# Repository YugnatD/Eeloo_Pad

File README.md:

# Eeloo Pad
## A Kerbal Space Program Control Panel
A Open Source project to create a control panel for Kerbal Space Program. The goal is to create a control panel that can be used to control the game from a physical panel. The control panel will be able to control the game, and display information about the game.

## Features
* Control the game (Thrust, SAS, RCS, etc.)
* TODO

## Block Diagram
[Diagram](https://app.diagrams.net/#G1_EMb1VFjsUEVt7AdRK-4kCuMEsyWomvp)

## Schematic

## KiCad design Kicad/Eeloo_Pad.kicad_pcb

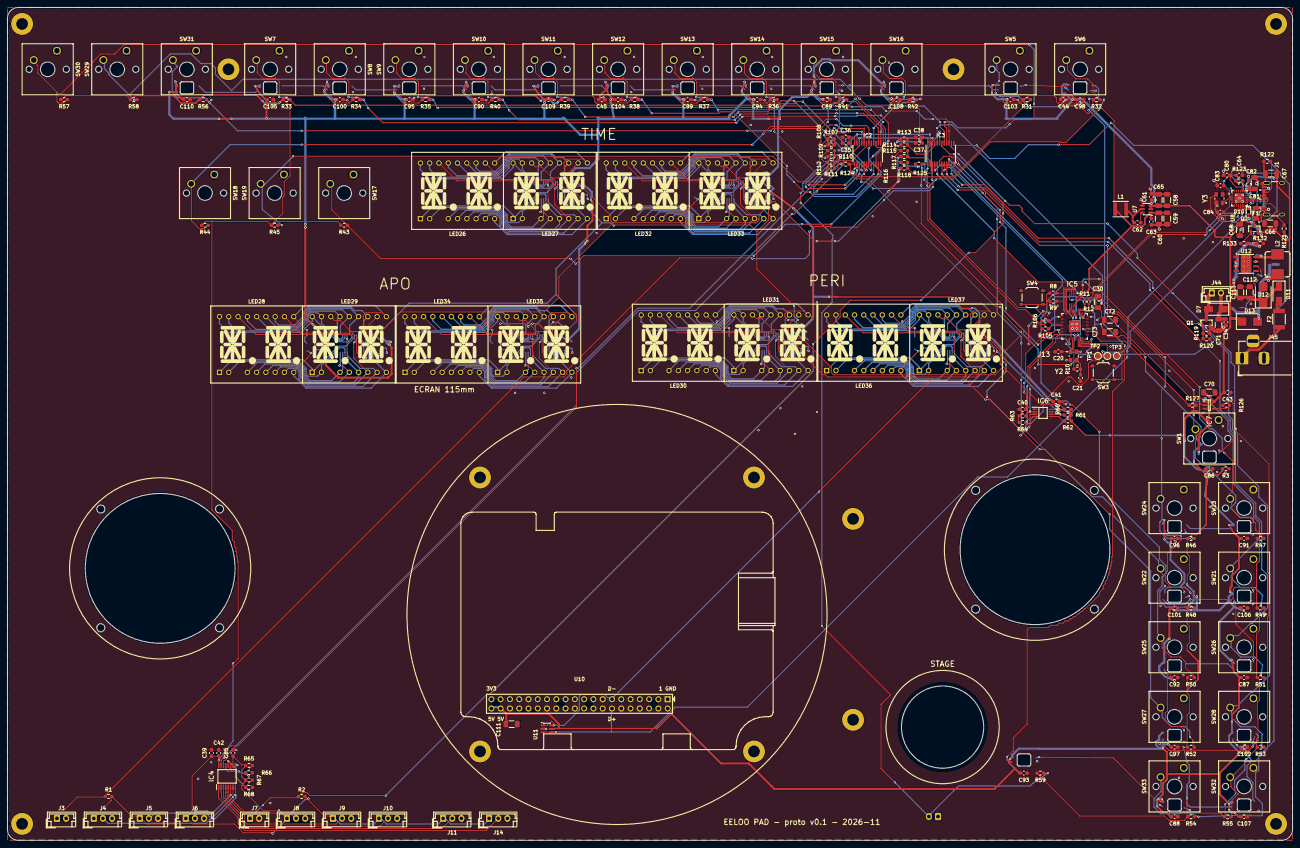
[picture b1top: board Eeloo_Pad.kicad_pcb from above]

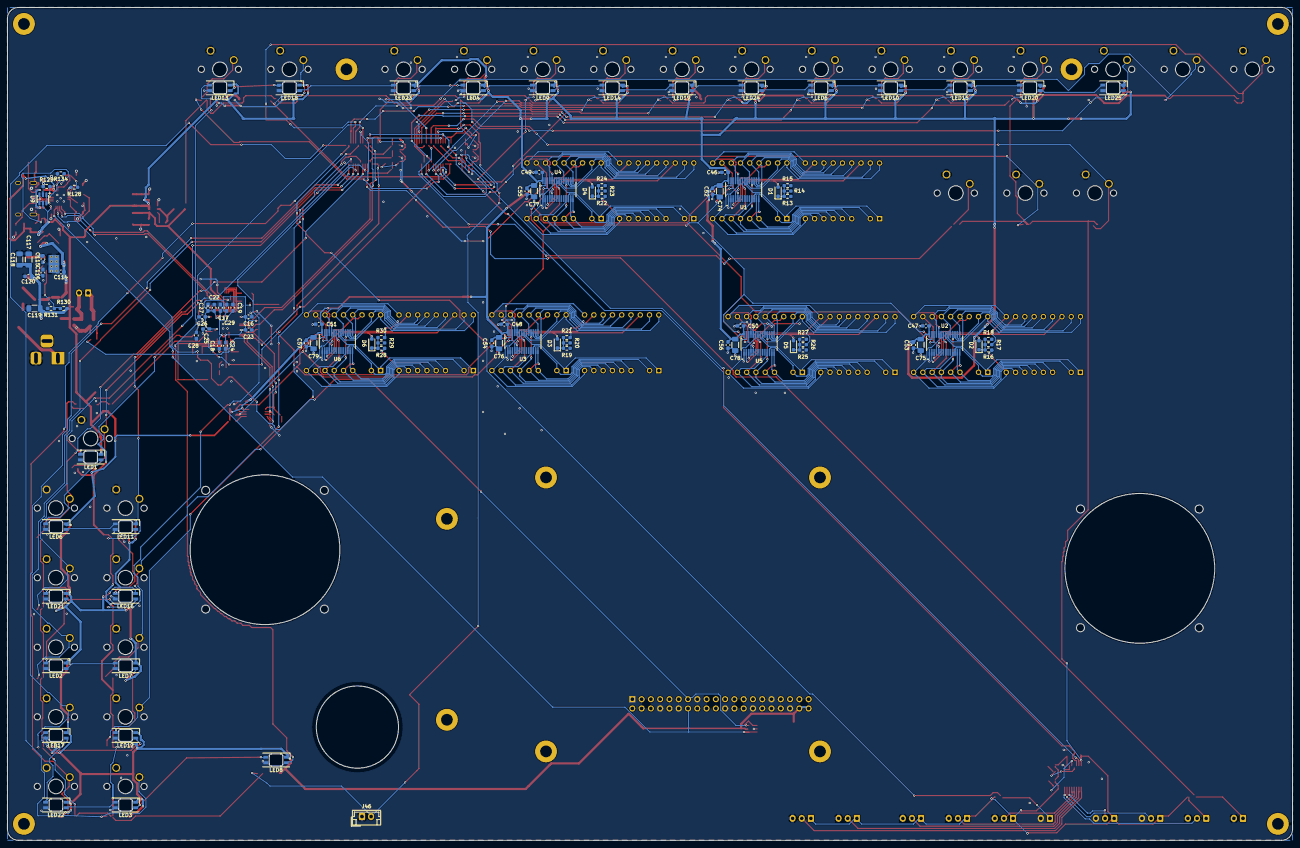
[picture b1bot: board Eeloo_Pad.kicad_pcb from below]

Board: 2 copper layers, 351.8 x 228.0 mm, 333 parts (99 on the bottom side), 253 nets.

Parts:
C16, C18, C19, C23, C24, C25, C26, C27, C28, C29, C34, C35, C36, C37, C38, C39, C40, C41, C42, C43, C44, C45, C46, C47, C48, C49, C50, C51, C52, C53, C54, C55, C56, C57, C64, C82, C85, C86, C87, C88, C89, C90, C91, C92, C93, C94, C95, C96, C97, C98, C99, C100, C101, C102, C103, C104, C105, C106, C107, C108, C109, C110: 100n; C_0603_1608Metric_Pad1.08x0.95mm_HandSolder
C17, C22, C80: 1u; C_0603_1608Metric_Pad1.08x0.95mm_HandSolder
C20, C21, C83, C84: 15p; C_0603_1608Metric_Pad1.08x0.95mm_HandSolder
C30, C81, C111: 10u; C_1206_3216Metric_Pad1.33x1.80mm_HandSolder
C58, C59, C60, C65, C66, C67, C68, C70, C71, C72, C73, C74, C75, C76, C77, C78, C79, C117, C118, C119: 22uF; C_1206_3216Metric_Pad1.33x1.80mm_HandSolder
C61, C62, C63, C114, C115, C120: 100nF; C_0603_1608Metric_Pad1.08x0.95mm_HandSolder
C112, C113: 10uF; C_1206_3216Metric_Pad1.33x1.80mm_HandSolder
C116: 1uF; C_0603_1608Metric_Pad1.08x0.95mm_HandSolder
D1, D2, D3, D4, D5, D6: SD103AWS; D_SOD-323_HandSoldering
D7, D11: SS34; D_SMA
D10: ESD5Zxx; D_SOD-523
D12: SMBJ15CA; D_SMB
D13: SS54; D_SMB
F1: 1.5A; Fuse_1206_3216Metric
F2: 2A; Fuse_1812_4532Metric_Pad1.30x3.40mm_HandSolder
H1, H2, H3, H4, H5, H6, H7, H8, H9, H10, H11, H12: MountingHole_3.2mm_M3_Pad
H13: XB2-BS542 22.5mm; Schneider_XB2_22.5mm_PanelMount
IC2, IC3: PCA9535PW; TSSOP-24_4.4x7.8mm_P0.65mm
IC4: ADS7830IPWR; SOP65P640X120-16N
IC5: W25Q16JVUXIQ_TR; SON50P300X200X60-9N
IC6: TCA9617ADGKR; SOP65P490X110-8N
IC7: SN74AHCT1G125DBVR; SOT95P280X145-5N
J1: USB_C_Receptacle_USB2.0_16P; USB_C_Receptacle_HCTL_HC-TYPE-C-16P-01A
J3, J7, J44: Conn_01x02_Pin; JST_EH_B2B-EH-A_1x02_P2.50mm_Vertical
J4, J5, J6, J8, J9, J10, J11, J14: Conn_01x03_Pin; JST_EH_B3B-EH-A_1x03_P2.50mm_Vertical
J13: SC0914_13_; SC091413
J45: Jack 12V 5.5x2.1; BarrelJack_Horizontal
J46: XB2-BS542 STAGE; JST_EH_B2B-EH-A_1x02_P2.50mm_Vertical
JS1, JS2: R400B-M2
L1: 3.9uH; L_Sunlord_SWPA4030S
L2: 8.2uH; L_Bourns_SRP7028A_7.3x6.6mm
LED1, LED2, LED3, LED4, LED5, LED6, LED7, LED8, LED9, LED10, LED11, LED12, LED13, LED14, LED15, LED16, LED17, LED18, LED19, LED20, LED21, LED22, LED23, LED24, LED25: SK6812MINI-EA; LED_SK6812MINI-E_3.2x2.8mm
LED26, LED27, LED28, LED29, LED30, LED31, LED32, LED33, LED34, LED35, LED36, LED37: FJ5241AH; LED-SEG-TH_18P-L25.2-W21.1-P2.54-LS15.2-BL
Q1: AO3400A; SOT-23
Q2: AO3401A; SOT-23
R1, R2, R3, R31, R32, R33, R34, R35, R36, R37, R38, R39, R40, R41, R42, R43, R44, R45, R46, R47, R48, R49, R50, R51, R52, R53, R54, R55, R56, R57, R58, R59, R62, R65, R66, R67, R68, R107, R108, R109, R110, R111, R112, R113, R114, R115, R116, R117, R118, R119, R123, R124, R125, R127, R128, R129: 10k; R_0603_1608Metric_Pad0.98x0.95mm_HandSolder
R8, R10: 1k; R_0603_1608Metric_Pad0.98x0.95mm_HandSolder
R9: NC; R_0603_1608Metric_Pad0.98x0.95mm_HandSolder
R11, R12: 27.4; R_0402_1005Metric_Pad0.72x0.64mm_HandSolder
R13, R14, R15, R16, R17, R18, R19, R20, R21, R22, R23, R24, R25, R26, R27, R28, R29, R30: 39k; R_0603_1608Metric_Pad0.98x0.95mm_HandSolder
R60, R61, R63, R64, R105, R106: 4k7; R_0603_1608Metric_Pad0.98x0.95mm_HandSolder
R120: 100; R_0603_1608Metric_Pad0.98x0.95mm_HandSolder
R121, R122: 5.1k; R_0603_1608Metric_Pad0.98x0.95mm_HandSolder
R126: 330; R_0603_1608Metric_Pad0.98x0.95mm_HandSolder
R130, R133: 100k; R_0603_1608Metric_Pad0.98x0.95mm_HandSolder
R131: 23.2k; R_0603_1608Metric_Pad0.98x0.95mm_HandSolder
R132: 47k; R_0603_1608Metric_Pad0.98x0.95mm_HandSolder
R134: 15k; R_0603_1608Metric_Pad0.98x0.95mm_HandSolder
SW1, SW5, SW6, SW7, SW8, SW9, SW10, SW11, SW12, SW13, SW14, SW15, SW16, SW17, SW18, SW19, SW21, SW22, SW23, SW24, SW25, SW26, SW27, SW28, SW29, SW30, SW31, SW32, SW33: DUROCK_Ice_King_62g; SW_MX_Transparent_1.00u_PCB
SW3, SW4: SW_Push; SW_Push_1P1T_XKB_TS-1187A
TP1: SWCLK; TestPoint_Pad_D1.5mm
TP2: SWDIO; TestPoint_Pad_D1.5mm
TP3: GND; TestPoint_Pad_D1.5mm
U1, U2, U3, U4, U5, U6: HT16K33A-28SSOP; SOP63P600X175-28N
U7: AP63203WU; TSOT-23-6
U8: CH334F; QFN-24-1EP_4x4mm_P0.5mm_EP2.7x2.7mm
U9, U11: USBLC6-2SC6; SOT-23-6
U10: ESP32-P4-WIFI6-Touch-LCD-3.4C; ESP32-P4_WS_3.4C_Header
U12: LMR33630ADDA; Texas_HSOP-8-1EP_3.9x4.9mm_P1.27mm_ThermalVias
Y2: ABM8-272-T3; ABM8272T3
Y3: 12MHz; ABM8272T3

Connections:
+3.3V: C16.1, C22.1, C23.1, C24.1, C25.1, C26.1, C27.1, C28.1, C29.1, C30.1, C35.1, C36.1, C37.1, C38.1, C39.1, C40.1, C42.1, C59.1, C60.1, C63.1, C72.1, C73.1, C85.1, IC2.24 (VCC), IC3.24 (VCC), IC4.10 (REFIN/REFOUT), IC4.16 (+VDD), IC5.8 (VCC), IC6.1 (VCC(A)), J4.1, J5.1, J6.1, J8.1, J9.1, J10.1, J11.1, J13.1 (IOVDD_1), J13.10 (IOVDD_2), J13.22 (IOVDD_3), J13.33 (IOVDD_4), J13.42 (IOVDD_5), J13.43 (ADC_AVDD), J13.44 (VREG_VIN), J13.48 (USB_VDD), J13.49 (IOVDD_6), J14.1, L1.2, R1.2, R2.2, R3.1, R9.2, R31.1, R32.1, R33.1, R34.1, R35.1, R36.1, R37.1, R38.1, R39.1, R40.1, R41.1, R42.1, R43.1, R44.1, R45.1, R46.1, R47.1, R48.1, R49.1, R50.1, R51.1, R52.1, R53.1, R54.1, R55.1, R56.1, R57.1, R58.1, R59.1, R63.1, R64.1, R65.1, R67.1, R105.1, R106.1, R107.1, R109.1, R111.1, R113.1, R115.1, R117.1, R124.1, R125.1, U7.1 (FB)
+12V: C112.1, C113.1, C114.1, D11.1, D12.1, R132.1, U12.2, U12.3
/BUCK_BOOT: C115.1, U12.7
/BUCK_FB: R130.2, R131.1, U12.5
/BUCK_SW: C115.2, L2.1, U12.8
/BUCK_VCC: C116.1, U12.6
/CC1: J1.A5 (CC1), R121.1
/CC2: J1.B5 (CC2), R122.1
/DC_SENSE: Q2.1, R132.2, R133.1
/HUB_OVCUR: R128.2, U8.1 (~OVCUR)
/HUB_PSELF: R129.1, U8.18 (PSELF)
/HUB_RESET: R123.2, R134.1, U8.16 (~RESET/CDP)
/HUB_V33: C64.1, C80.1, R128.1, U8.20 (VDD33_{LDO})
/USB1_DM: U8.11 (DM1-), U10.13 (GPIO20_27), U11.1 (I/O1), U11.6 (I/O1)
/USB1_DP: U8.12 (DP1+), U10.14 (GND_28), U11.3 (I/O2), U11.4 (I/O2)
/USB2_DM: R12.2, U8.9 (DM2-)
/USB2_DP: R11.2, U8.10 (DP2+)
/USB_DM: J1.A7 (D-), J1.B7 (D-), U8.14 (DMU-), U9.1 (I/O1), U9.6 (I/O1)
/USB_DP: J1.A6 (D+), J1.B6 (D+), U8.15 (DPU+), U9.3 (I/O2), U9.4 (I/O2)
/V5_DC: C117.1, C118.1, C119.1, C120.1, D13.2, L2.2, R130.1
/VBUS: C34.1, C41.1, C43.1, C44.1, C45.1, C46.1, C47.1, C48.1, C49.1, C50.1, C51.1, C52.1, C53.1, C54.1, C55.1, C56.1, C57.1, C58.1, C61.1, C65.1, C66.1, C67.1, C68.1, C70.1, C71.1, C74.1, C75.1, C76.1, C77.1, C78.1, C79.1, C81.1, C82.1, C86.1, C87.1, C88.1, C89.1, C90.1, C91.1, C92.1, C93.1, C94.1, C95.1, C96.1, C97.1, C98.1, C99.1, C100.1, C101.1, C102.1, C103.1, C104.1, C105.1, C106.1, C107.1, C108.1, C109.1, C110.1, C111.1, D7.1 (K), D10.1 (K), D13.1, IC6.8 (VCC(B)), IC7.5 (VCC), J44.2, LED1.1, LED2.1, LED3.1, LED4.1, LED5.1, LED6.1, LED7.1, LED8.1, LED9.1, LED10.1, LED11.1, LED12.1, LED13.1, LED14.1, LED15.1, LED16.1, LED17.1, LED18.1, LED19.1, LED20.1, LED21.1, LED22.1, LED23.1, LED24.1, LED25.1, Q2.2, R60.1, R61.1, R62.1, U1.28 (VDD), U2.28 (VDD), U3.28 (VDD), U4.28 (VDD), U5.28 (VDD), U6.28 (VDD), U7.2 (EN), U7.3 (IN), U8.19 (V5), U9.5 (VBUS), U10.38 (GPIO46_4), U10.40 (GPIO30_2), U11.5 (VBUS)
/VBUS_USB: F1.2, Q2.3, R123.1
/control_module/ANTINORMAL: IC3.7 (P03), R49.2, SW21.2
/control_module/ANTI_MANEUVER: IC3.14 (P11), R55.2, SW32.2
/control_module/ANTI_TARGET: IC3.11 (P07), R53.2, SW28.2
/control_module/BRAKE: IC2.19 (P16), R45.2, SW19.2
/control_module/CIBLE_ORBIT: IC3.15 (P12), R56.2, SW31.2
/control_module/CTRL0: IC2.6 (P02), R33.2, SW7.2
/control_module/CTRL1: IC2.7 (P03), R34.2, SW8.2
/control_module/CTRL2: IC2.8 (P04), R35.2, SW9.2
/control_module/CTRL3: IC2.9 (P05), R36.2, SW14.2
/control_module/CTRL4: IC2.10 (P06), R37.2, SW13.2
/control_module/CTRL5: IC2.11 (P07), R38.2, SW12.2
/control_module/CTRL6: IC2.13 (P10), R39.2, SW11.2
/control_module/CTRL7: IC2.14 (P11), R40.2, SW10.2
/control_module/CTRL8: IC2.15 (P12), R41.2, SW15.2
/control_module/CTRL9: IC2.16 (P13), R42.2, SW16.2
/control_module/EXT1: IC4.1 (CH0), J14.2
/control_module/GEAR: IC2.18 (P15), R44.2, SW18.2
/control_module/I2C0_SCL_33: IC2.22 (SCL), IC3.22 (SCL), IC4.14 (SCL), J13.7 (GPIO5), R105.2
/control_module/I2C0_SDA_33: IC2.23 (SDA), IC3.23 (SDA), IC4.15 (SDA), J13.6 (GPIO4), R106.2
/control_module/I2C1_SCL_33: IC6.2 (SCLA), J13.14 (GPIO11), R63.2
/control_module/I2C1_SCL_50: IC6.7 (SCLB), R60.2, U1.26 (SCL), U2.26 (SCL), U3.26 (SCL), U4.26 (SCL), U5.26 (SCL), U6.26 (SCL)
/control_module/I2C1_SDA_33: IC6.3 (SDAA), J13.13 (GPIO10), R64.2
/control_module/I2C1_SDA_50: IC6.6 (SDAB), R61.2, U1.27 (SDA), U2.27 (SDA), U3.27 (SDA), U4.27 (SDA), U5.27 (SDA), U6.27 (SDA)
/control_module/I2C_GPIO_EXT0_INT: IC2.1 (~INT), J13.18 (GPIO15), R124.2
/control_module/I2C_GPIO_EXT1_INT: IC3.1 (~INT), J13.27 (GPIO16), R125.2
/control_module/JOY_BTN_D: IC3.18 (P15), J7.1, R2.1
/control_module/JOY_BTN_G: IC3.19 (P16), J3.1, R1.1
/control_module/JOY_D_AXIS_R: IC4.3 (CH2), J10.2
/control_module/JOY_D_AXIS_X: IC4.5 (CH4), J8.2
/control_module/JOY_D_AXIS_Y: IC4.4 (CH3), J9.2
/control_module/JOY_G_AXIS_R: IC4.6 (CH5), J6.2
/control_module/JOY_G_AXIS_X: IC4.8 (CH7), J4.2
/control_module/JOY_G_AXIS_Y: IC4.7 (CH6), J5.2
/control_module/LED_CTRL_33: IC7.2 (A), J13.32 (GPIO21), R127.1
/control_module/LED_CTRL_50: IC7.4 (Y), R126.2
/control_module/LIGHT: IC2.17 (P14), R43.2, SW17.2
/control_module/MANEUVER: IC3.13 (P10), R54.2, SW33.2
/control_module/NORMAL: IC3.6 (P02), R48.2, SW22.2
/control_module/ORBIT_SURFACE: IC3.16 (P13), R57.2, SW30.2
/control_module/PROGRADE: IC3.4 (P00), R46.2, SW24.2
/control_module/RADIAL_IN: IC3.8 (P04), R50.2, SW25.2
/control_module/RADIAL_OUT: IC3.9 (P05), R51.2, SW26.2
/control_module/RCS: IC2.5 (P01), R32.2, SW6.2
/control_module/RETROGRADE: IC3.5 (P01), R47.2, SW23.2
/control_module/SAS: IC2.4 (P00), R31.2, SW5.2
/control_module/SEA_EARTH: IC3.17 (P14), R58.2, SW29.2
/control_module/STAB_ASSIST: IC3.20 (P17), R3.2, SW1.2
/control_module/STAGE: IC2.20 (P17), J46.2, R59.2
/control_module/TARGET: IC3.10 (P06), R52.2, SW27.2
/control_module/THROTTLE: IC4.2 (CH1), J11.2
/control_module/VIBRO_CTRL_33: J13.17 (GPIO14), R120.1
/control_module/seg_4x14_module1/A: LED32.12 (A), LED33.12 (A), U4.25 (ROW0/A2)
/control_module/seg_4x14_module1/A0: LED32.9 (C), LED33.9 (C), R22.1, U4.23 (ROW2/A0)
/control_module/seg_4x14_module1/A1: LED32.10 (B), LED33.10 (B), U4.24 (ROW1/A1)
/control_module/seg_4x14_module1/AD: D4.2 (A), LED32.16 (DIG1), U4.2 (COM0/AD)
/control_module/seg_4x14_module1/COM1: LED32.11 (DIG2), U4.3 (COM1/KS0)
/control_module/seg_4x14_module1/COM2: LED33.16 (DIG1), U4.4 (COM2/KS1)
/control_module/seg_4x14_module1/COM3: LED33.11 (DIG2), U4.5 (COM3/KS2)
/control_module/seg_4x14_module1/D: LED32.7 (D), LED33.7 (D), U4.22 (ROW3/K1)
/control_module/seg_4x14_module1/DP: LED32.8 (DP), LED33.8 (DP), U4.11 (ROW14/K12)
/control_module/seg_4x14_module1/E: LED32.1 (E), LED33.1 (E), U4.21 (ROW4/K2)
/control_module/seg_4x14_module1/F: LED32.18 (F), LED33.18 (F), U4.20 (ROW5/K3)
/control_module/seg_4x14_module1/G1: LED32.13 (G1), LED33.13 (G1), U4.19 (ROW6/K4)
/control_module/seg_4x14_module1/G2: LED32.6 (G2), LED33.6 (G2), U4.18 (ROW7/K5)
/control_module/seg_4x14_module1/H: LED32.17 (H), LED33.17 (H), U4.17 (ROW8/K6)
/control_module/seg_4x14_module1/J: LED32.15 (J), LED33.15 (J), U4.16 (ROW9/K7)
/control_module/seg_4x14_module1/K: LED32.14 (K), LED33.14 (K), U4.15 (ROW10/K8)
/control_module/seg_4x14_module1/L: LED32.5 (L), LED33.5 (L), U4.14 (ROW11/K9)
/control_module/seg_4x14_module1/M: LED32.4 (M), LED33.4 (M), U4.13 (ROW12/K10)
/control_module/seg_4x14_module1/N: LED32.2 (N), LED33.2 (N), U4.12 (ROW13/K11)
/control_module/seg_4x14_module2/A: LED34.12 (A), LED35.12 (A), U5.25 (ROW0/A2)
/control_module/seg_4x14_module2/A0: LED34.9 (C), LED35.9 (C), U5.23 (ROW2/A0)
/control_module/seg_4x14_module2/A1: LED34.10 (B), LED35.10 (B), R26.1, U5.24 (ROW1/A1)
/control_module/seg_4x14_module2/AD: D5.2 (A), LED34.16 (DIG1), U5.2 (COM0/AD)
/control_module/seg_4x14_module2/COM1: LED34.11 (DIG2), U5.3 (COM1/KS0)
/control_module/seg_4x14_module2/COM2: LED35.16 (DIG1), U5.4 (COM2/KS1)
/control_module/seg_4x14_module2/COM3: LED35.11 (DIG2), U5.5 (COM3/KS2)
/control_module/seg_4x14_module2/D: LED34.7 (D), LED35.7 (D), U5.22 (ROW3/K1)
/control_module/seg_4x14_module2/DP: LED34.8 (DP), LED35.8 (DP), U5.11 (ROW14/K12)
/control_module/seg_4x14_module2/E: LED34.1 (E), LED35.1 (E), U5.21 (ROW4/K2)
/control_module/seg_4x14_module2/F: LED34.18 (F), LED35.18 (F), U5.20 (ROW5/K3)
/control_module/seg_4x14_module2/G1: LED34.13 (G1), LED35.13 (G1), U5.19 (ROW6/K4)
/control_module/seg_4x14_module2/G2: LED34.6 (G2), LED35.6 (G2), U5.18 (ROW7/K5)
/control_module/seg_4x14_module2/H: LED34.17 (H), LED35.17 (H), U5.17 (ROW8/K6)
/control_module/seg_4x14_module2/J: LED34.15 (J), LED35.15 (J), U5.16 (ROW9/K7)
/control_module/seg_4x14_module2/K: LED34.14 (K), LED35.14 (K), U5.15 (ROW10/K8)
/control_module/seg_4x14_module2/L: LED34.5 (L), LED35.5 (L), U5.14 (ROW11/K9)
/control_module/seg_4x14_module2/M: LED34.4 (M), LED35.4 (M), U5.13 (ROW12/K10)
/control_module/seg_4x14_module2/N: LED34.2 (N), LED35.2 (N), U5.12 (ROW13/K11)
/control_module/seg_4x14_module3/A: LED28.12 (A), LED29.12 (A), U2.25 (ROW0/A2)
/control_module/seg_4x14_module3/A0: LED28.9 (C), LED29.9 (C), R16.1, U2.23 (ROW2/A0)
/control_module/seg_4x14_module3/A1: LED28.10 (B), LED29.10 (B), R17.1, U2.24 (ROW1/A1)
/control_module/seg_4x14_module3/AD: D2.2 (A), LED28.16 (DIG1), U2.2 (COM0/AD)
/control_module/seg_4x14_module3/COM1: LED28.11 (DIG2), U2.3 (COM1/KS0)
/control_module/seg_4x14_module3/COM2: LED29.16 (DIG1), U2.4 (COM2/KS1)
/control_module/seg_4x14_module3/COM3: LED29.11 (DIG2), U2.5 (COM3/KS2)
/control_module/seg_4x14_module3/D: LED28.7 (D), LED29.7 (D), U2.22 (ROW3/K1)
/control_module/seg_4x14_module3/DP: LED28.8 (DP), LED29.8 (DP), U2.11 (ROW14/K12)
/control_module/seg_4x14_module3/E: LED28.1 (E), LED29.1 (E), U2.21 (ROW4/K2)
/control_module/seg_4x14_module3/F: LED28.18 (F), LED29.18 (F), U2.20 (ROW5/K3)
/control_module/seg_4x14_module3/G1: LED28.13 (G1), LED29.13 (G1), U2.19 (ROW6/K4)
/control_module/seg_4x14_module3/G2: LED28.6 (G2), LED29.6 (G2), U2.18 (ROW7/K5)
/control_module/seg_4x14_module3/H: LED28.17 (H), LED29.17 (H), U2.17 (ROW8/K6)
/control_module/seg_4x14_module3/J: LED28.15 (J), LED29.15 (J), U2.16 (ROW9/K7)
/control_module/seg_4x14_module3/K: LED28.14 (K), LED29.14 (K), U2.15 (ROW10/K8)
/control_module/seg_4x14_module3/L: LED28.5 (L), LED29.5 (L), U2.14 (ROW11/K9)
/control_module/seg_4x14_module3/M: LED28.4 (M), LED29.4 (M), U2.13 (ROW12/K10)
/control_module/seg_4x14_module3/N: LED28.2 (N), LED29.2 (N), U2.12 (ROW13/K11)
/control_module/seg_4x14_module4/A: LED30.12 (A), LED31.12 (A), R21.1, U3.25 (ROW0/A2)
/control_module/seg_4x14_module4/A0: LED30.9 (C), LED31.9 (C), U3.23 (ROW2/A0)
/control_module/seg_4x14_module4/A1: LED30.10 (B), LED31.10 (B), U3.24 (ROW1/A1)
/control_module/seg_4x14_module4/AD: D3.2 (A), LED30.16 (DIG1), U3.2 (COM0/AD)
/control_module/seg_4x14_module4/COM1: LED30.11 (DIG2), U3.3 (COM1/KS0)
/control_module/seg_4x14_module4/COM2: LED31.16 (DIG1), U3.4 (COM2/KS1)
/control_module/seg_4x14_module4/COM3: LED31.11 (DIG2), U3.5 (COM3/KS2)
/control_module/seg_4x14_module4/D: LED30.7 (D), LED31.7 (D), U3.22 (ROW3/K1)
/control_module/seg_4x14_module4/DP: LED30.8 (DP), LED31.8 (DP), U3.11 (ROW14/K12)
/control_module/seg_4x14_module4/E: LED30.1 (E), LED31.1 (E), U3.21 (ROW4/K2)
/control_module/seg_4x14_module4/F: LED30.18 (F), LED31.18 (F), U3.20 (ROW5/K3)
/control_module/seg_4x14_module4/G1: LED30.13 (G1), LED31.13 (G1), U3.19 (ROW6/K4)
/control_module/seg_4x14_module4/G2: LED30.6 (G2), LED31.6 (G2), U3.18 (ROW7/K5)
/control_module/seg_4x14_module4/H: LED30.17 (H), LED31.17 (H), U3.17 (ROW8/K6)
/control_module/seg_4x14_module4/J: LED30.15 (J), LED31.15 (J), U3.16 (ROW9/K7)
/control_module/seg_4x14_module4/K: LED30.14 (K), LED31.14 (K), U3.15 (ROW10/K8)
/control_module/seg_4x14_module4/L: LED30.5 (L), LED31.5 (L), U3.14 (ROW11/K9)
/control_module/seg_4x14_module4/M: LED30.4 (M), LED31.4 (M), U3.13 (ROW12/K10)
/control_module/seg_4x14_module4/N: LED30.2 (N), LED31.2 (N), U3.12 (ROW13/K11)
/control_module/seg_4x14_module5/A: LED36.12 (A), LED37.12 (A), R30.1, U6.25 (ROW0/A2)
/control_module/seg_4x14_module5/A0: LED36.9 (C), LED37.9 (C), R28.1, U6.23 (ROW2/A0)
/control_module/seg_4x14_module5/A1: LED36.10 (B), LED37.10 (B), U6.24 (ROW1/A1)
/control_module/seg_4x14_module5/AD: D6.2 (A), LED36.16 (DIG1), U6.2 (COM0/AD)
/control_module/seg_4x14_module5/COM1: LED36.11 (DIG2), U6.3 (COM1/KS0)
/control_module/seg_4x14_module5/COM2: LED37.16 (DIG1), U6.4 (COM2/KS1)
/control_module/seg_4x14_module5/COM3: LED37.11 (DIG2), U6.5 (COM3/KS2)
/control_module/seg_4x14_module5/D: LED36.7 (D), LED37.7 (D), U6.22 (ROW3/K1)
/control_module/seg_4x14_module5/DP: LED36.8 (DP), LED37.8 (DP), U6.11 (ROW14/K12)
/control_module/seg_4x14_module5/E: LED36.1 (E), LED37.1 (E), U6.21 (ROW4/K2)
/control_module/seg_4x14_module5/F: LED36.18 (F), LED37.18 (F), U6.20 (ROW5/K3)
/control_module/seg_4x14_module5/G1: LED36.13 (G1), LED37.13 (G1), U6.19 (ROW6/K4)
/control_module/seg_4x14_module5/G2: LED36.6 (G2), LED37.6 (G2), U6.18 (ROW7/K5)
/control_module/seg_4x14_module5/H: LED36.17 (H), LED37.17 (H), U6.17 (ROW8/K6)
/control_module/seg_4x14_module5/J: LED36.15 (J), LED37.15 (J), U6.16 (ROW9/K7)
/control_module/seg_4x14_module5/K: LED36.14 (K), LED37.14 (K), U6.15 (ROW10/K8)
/control_module/seg_4x14_module5/L: LED36.5 (L), LED37.5 (L), U6.14 (ROW11/K9)
/control_module/seg_4x14_module5/M: LED36.4 (M), LED37.4 (M), U6.13 (ROW12/K10)
/control_module/seg_4x14_module5/N: LED36.2 (N), LED37.2 (N), U6.12 (ROW13/K11)
/control_module/seg_4x14_module/A: LED26.12 (A), LED27.12 (A), U1.25 (ROW0/A2)
/control_module/seg_4x14_module/A0: LED26.9 (C), LED27.9 (C), U1.23 (ROW2/A0)
/control_module/seg_4x14_module/A1: LED26.10 (B), LED27.10 (B), U1.24 (ROW1/A1)
/control_module/seg_4x14_module/AD: D1.2 (A), LED26.16 (DIG1), U1.2 (COM0/AD)
/control_module/seg_4x14_module/COM1: LED26.11 (DIG2), U1.3 (COM1/KS0)
/control_module/seg_4x14_module/COM2: LED27.16 (DIG1), U1.4 (COM2/KS1)
/control_module/seg_4x14_module/COM3: LED27.11 (DIG2), U1.5 (COM3/KS2)
/control_module/seg_4x14_module/D: LED26.7 (D), LED27.7 (D), U1.22 (ROW3/K1)
/control_module/seg_4x14_module/DP: LED26.8 (DP), LED27.8 (DP), U1.11 (ROW14/K12)
/control_module/seg_4x14_module/E: LED26.1 (E), LED27.1 (E), U1.21 (ROW4/K2)
/control_module/seg_4x14_module/F: LED26.18 (F), LED27.18 (F), U1.20 (ROW5/K3)
/control_module/seg_4x14_module/G1: LED26.13 (G1), LED27.13 (G1), U1.19 (ROW6/K4)
/control_module/seg_4x14_module/G2: LED26.6 (G2), LED27.6 (G2), U1.18 (ROW7/K5)
/control_module/seg_4x14_module/H: LED26.17 (H), LED27.17 (H), U1.17 (ROW8/K6)
/control_module/seg_4x14_module/J: LED26.15 (J), LED27.15 (J), U1.16 (ROW9/K7)
/control_module/seg_4x14_module/K: LED26.14 (K), LED27.14 (K), U1.15 (ROW10/K8)
/control_module/seg_4x14_module/L: LED26.5 (L), LED27.5 (L), U1.14 (ROW11/K9)
/control_module/seg_4x14_module/M: LED26.4 (M), LED27.4 (M), U1.13 (ROW12/K10)
/control_module/seg_4x14_module/N: LED26.2 (N), LED27.2 (N), U1.12 (ROW13/K11)
/control_module/uC1/+1.1V: C17.1, C18.1, C19.1, J13.23 (DVDD_1), J13.45 (VREG_VOUT), J13.50 (DVDD_2)
/control_module/uC1/QSPI_SCLK: IC5.6 (CLK), J13.52 (QSPI_SCLK)
/control_module/uC1/QSPI_SD0: IC5.5 (DI(IO0)), J13.53 (QSPI_SD0)
/control_module/uC1/QSPI_SD1: IC5.2 (DO(IO1)), J13.55 (QSPI_SD1)
/control_module/uC1/QSPI_SD2: IC5.3 (IO2), J13.54 (QSPI_SD2)
/control_module/uC1/QSPI_SD3: IC5.7 (IO3), J13.51 (QSPI_SD3)
/control_module/uC1/QSPI_SS: IC5.1 (~CS), J13.56 (QSPI_SS_N), R8.1, R9.1
/control_module/uC1/RUN: J13.26 (RUN), SW3.2
/control_module/uC1/SWCLK: J13.24 (SWCLK), TP1.1 (1_1)
/control_module/uC1/SWD: J13.25 (SWDIO), TP2.1 (1_1)
/control_module/uC1/XIN: C20.2, J13.20 (XIN), Y2.1
/control_module/uC1/XOUT: J13.21 (XOUT), R10.2
GND: C16.2, C17.2, C18.2, C19.2, C20.1, C21.1, C22.2, C23.2, C24.2, C25.2, C26.2, C27.2, C28.2, C29.2, C30.2, C34.2, C35.2, C36.2, C37.2, C38.2, C39.2, C40.2, C41.2, C42.2, C43.2, C44.2, C45.2, C46.2, C47.2, C48.2, C49.2, C50.2, C51.2, C52.2, C53.2, C54.2, C55.2, C56.2, C57.2, C58.2, C59.2, C60.2, C61.2, C63.2, C64.2, C65.2, C66.2, C67.2, C68.2, C70.2, C71.2, C72.2, C73.2, C74.2, C75.2, C76.2, C77.2, C78.2, C79.2, C80.2, C81.2, C82.2, C83.1, C84.1, C85.2, C86.2, C87.2, C88.2, C89.2, C90.2, C91.2, C92.2, C93.2, C94.2, C95.2, C96.2, C97.2, C98.2, C99.2, C100.2, C101.2, C102.2, C103.2, C104.2, C105.2, C106.2, C107.2, C108.2, C109.2, C110.2, C111.2, C112.2, C113.2, C114.2, C116.2, C117.2, C118.2, C119.2, C120.2, D10.2 (A), D12.2, IC2.12 (GND), IC3.12 (GND), IC4.9 (GND), IC4.11 (COM), IC5.4 (GND), IC5.9 (EP), IC6.4 (GND), IC7.1 (~OE), IC7.3 (GND), J1.A1 (GND), J1.A12 (GND), J1.B1 (GND), J1.B12 (GND), J1.S1 (SHIELD), J3.2, J4.3, J5.3, J6.3, J7.2, J8.3, J9.3, J10.3, J11.3, J13.19 (TESTEN), J13.57 (GND), J14.3, J45.2, J46.1, LED1.3, LED2.3, LED3.3, LED4.3, LED5.3, LED6.3, LED7.3, LED8.3, LED9.3, LED10.3, LED11.3, LED12.3, LED13.3, LED14.3, LED15.3, LED16.3, LED17.3, LED18.3, LED19.3, LED20.3, LED21.3, LED22.3, LED23.3, LED24.3, LED25.3, Q1.2 (S), R66.2, R68.2, R108.2, R110.2, R112.2, R114.2, R116.2, R118.2, R119.2, R121.2, R122.2, R127.2, R129.2, R131.2, R133.2, R134.2, SW1.1, SW3.1, SW4.1, SW5.1, SW6.1, SW7.1, SW8.1, SW9.1, SW10.1, SW11.1, SW12.1, SW13.1, SW14.1, SW15.1, SW16.1, SW17.1, SW18.1, SW19.1, SW21.1, SW22.1, SW23.1, SW24.1, SW25.1, SW26.1, SW27.1, SW28.1, SW29.1, SW30.1, SW31.1, SW32.1, SW33.1, TP3.1 (1_1), U1.1 (VSS), U2.1 (VSS), U3.1 (VSS), U4.1 (VSS), U5.1 (VSS), U6.1 (VSS), U7.4 (GND), U8.25 (GND), U9.2 (GND), U10.1 (3V3_39), U10.8 (GPIO37_34), U10.12 (GPIO22_30), U10.15 (GPIO28_25), U10.22 (GPIO35_20), U10.28 (USB_DP_14), U10.31 (GPIO32_9), U10.36 (GPIO31_6), U11.2 (GND), U12.1, U12.9, Y2.2, Y2.4, Y3.2 (G), Y3.4 (G)
unnamed: C21.2, R10.1, Y2.3
unnamed: D1.1 (K), R13.2, R14.2, R15.2
unnamed: D2.1 (K), R16.2, R17.2, R18.2
unnamed: D3.1 (K), R19.2, R20.2, R21.2
unnamed: D4.1 (K), R22.2, R23.2, R24.2
unnamed: D5.1 (K), R25.2, R26.2, R27.2
unnamed: D6.1 (K), R28.2, R29.2, R30.2
unnamed: D7.2 (A), J44.1, Q1.3 (D)
unnamed: D11.2, F2.2
unnamed: F1.1, J1.A4 (VBUS), J1.A9 (VBUS), J1.B4 (VBUS), J1.B9 (VBUS)
unnamed: F2.1, J45.1
unnamed: IC2.21 (A0), R107.2, R108.1
unnamed: IC2.2 (A1), R109.2, R110.1
unnamed: IC2.3 (A2), R111.2, R112.1
unnamed: IC3.21 (A0), R113.2, R114.1
unnamed: IC3.2 (A1), R115.2, R116.1
unnamed: IC3.3 (A2), R117.2, R118.1
unnamed: IC4.12 (A0), R67.2, R68.1
unnamed: IC4.13 (A1), R65.2, R66.1
unnamed: IC6.5 (EN), R62.2
unnamed: J13.46 (USB_DM), R12.1
unnamed: J13.47 (USB_DP), R11.1
unnamed: LED1.4, R126.1
unnamed: LED1.2, LED6.4
unnamed: LED2.4, LED21.2
unnamed: LED2.2, LED7.4
unnamed: LED3.2, LED8.4
unnamed: LED4.2, LED9.4
unnamed: LED5.2, LED10.4
unnamed: LED10.2, LED15.4
unnamed: LED6.2, LED11.4
unnamed: LED11.2, LED16.4
unnamed: LED7.2, LED12.4
unnamed: LED12.2, LED17.4
unnamed: LED8.2, LED13.4
unnamed: LED13.2, LED18.4
unnamed: LED9.2, LED14.4
unnamed: LED14.2, LED19.4
unnamed: LED15.2, LED20.4
unnamed: LED16.2, LED21.4
unnamed: LED17.2, LED22.4
unnamed: LED18.2, LED23.4
unnamed: LED19.2, LED24.4
unnamed: LED20.2, LED25.4
unnamed: LED3.4, LED22.2
unnamed: LED4.4, LED23.2
unnamed: LED5.4, LED24.2
unnamed: Q1.1 (G), R119.1, R120.2
unnamed: R8.2, SW4.2
unnamed: C62.1, U7.6 (BST)
unnamed: C62.2, L1.1, U7.5 (SW)
unnamed: C84.2, U8.4 (XI), Y3.3
unnamed: C83.2, U8.3 (XO), Y3.1

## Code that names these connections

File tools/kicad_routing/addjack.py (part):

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place('Device:C', 'C115', '100nF', 228.6, 88.9, 90, {'1': 'BUCK_BOOT', '2': 'BUCK_SW'}, fp=C06, desc='bootstrap')
place('Device:L', 'L2', '8.2uH', 238.76, 101.6, 90, {'1': '-', '2': 'V5_DC'},
      fp='Inductor_SMD:L_Bourns_SRP1038C_10.0x10.0mm', desc='8.2uH, Isat >= 5A (e.g. Bourns SRP1038C-8R2M)')
wire(PP[('U12', '8')], PP[('L2', '1')]); label('BUCK_SW', 223.52, 101.6, (1, 0))
place('Device:R', 'R130', '100k', 242.57, 109.22, 0, {'1': '-', '2': '-'}, fp=R06, desc='FB top: Vout = 1.0V x (1 + 100k/23.2k) = 5.31V')
place('Device:R', 'R131', '23.2k', 242.57, 119.38, 0, {'1': '-', '2': 'GND'}, fp=R06, desc='FB bottom')
wire(PP[('L2', '2')], PP[('R130', '1')]); junction(*PP[('L2', '2')])
fa, fb = PP[('R130', '2')], PP[('R131', '1')]
wire(fa, fb); mid = (fa[0], (fa[1] + fb[1]) / 2); mid = (mid[0], round(mid[1] / 1.27) * 1.27)
junction(*mid); wire(mid, (mid[0] - 3.81, mid[1])); label('BUCK_FB', mid[0] - 3.81, mid[1], (-1, 0))
for i, x in enumerate((251.46, 261.62, 271.78)):
    place('Device:C', 'C%d' % (117 + i), '22uF', x, 111.76, 0, {'1': 'V5_DC', '2': 'GND'}, fp=C12, desc='output cap, 10V X7R')
place('Device:C', 'C120', '100nF', 281.94, 111.76, 0, {'1': 'V5_DC', '2': 'GND'}, fp=C06)
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place('Device:R', 'R133', '100k', 116.84, 139.7, 0, {'1': '-', '2': 'GND'}, fp=R06)
ga, gb = PP[('R132', '2')], PP[('R133', '1')]
wire(ga, gb); g = PP[('Q2', '1')]
junction(ga[0], g[1]); wire((ga[0], g[1]), g); label('DC_SENSE', ga[0] + 2.54, g[1], (1, 0)) if False else None
ITEMS.append('\t(label "DC_SENSE"\n\t\t(at %s %s 0)\n\t\t(effects\n\t\t\t(font\n\t\t\t\t(size 1.27 1.27)\n\t\t\t)\n\t\t\t(justify left bottom)\n\t\t)\n\t\t(uuid "%s")\n\t)\n' % (F(ga[0] + 2.54), F(g[1]), U()))
# --- power flags
def flag_on(net, x, y):
    if net == '+12V':
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    m = pat.search(s)
    assert m, (old, x, y)
    s = s[:m.start()] + '(label "%s"' % new + s[m.start() + len('(label "%s"' % old):]
relabel('VBUS', 'VBUS_USB', 58.42, 25.4)        # F1 pin 2 -> VBUS_USB
relabel('HUB_V33', 'VBUS_USB', 106.68, 22.86)   # R123 top -> VBUS_USB

# ---------------------------------------------------------------- insert before sheet_instances / embedded files end
k = s.rfind('\n\t(sheet_instances')
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
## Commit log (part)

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2023-03-10 Adding empty BOM and modification of the README
2023-03-10 Adding link to Block Diagram
2023-03-14 Adding a template for the communication mod
2023-03-14 Adding Project for KSP1
2023-03-15 Modification of the structure
2023-03-15 Print working without crash
2023-03-15 Adding Socket template for communication
2023-03-15 Casting data seem to work
2023-03-15 Reading XML + Better managing of the socket
2023-03-16 Can control the SAS through socket + Disabling the timer when not in flight
2023-03-16 Adding attribute to structure
2023-03-16 Tried adding more attribut
2023-03-17 Decoding of the vesselPacket seem to work
2023-03-17 Getting data and control with python from the socket seems to work
2023-03-17 Adding comment
2023-03-17 Some CleanUp for the Python
2023-03-17 Minor timing correction + remove Debug.Log
2023-04-04 Tried something for the navball
2023-04-05 Working on the C version for the navball
2023-04-06 Added more function for navball in C
2023-04-06 Navball close to working version in C
2023-04-20 Good value, but the result is not correct
2023-07-07 working c version to generate navball
2023-07-08 Modification to make computation on the stack for uC usage, need some optimisation
2023-07-08 Some optimisation
2023-07-08 Optimisation and adding yaw
2023-07-08 now everything is on stack, and the texture is stored on a c file
2023-07-08 tried to run navball on lpc54s018
2023-07-08 Really Optimised version
2023-07-09 Navball Working on LPC
2023-07-15 Tried to optimise
2023-10-11 adding last file from my pc
2023-10-11 Started to write a code in fixed point
2023-12-07 precalculed sin/cos
2023-12-23 adding formula
2023-12-25 some optimisation + writing of a mt version
2024-08-05 working version with precomputed value
2024-08-05 some cleanup
2024-08-08 minor correction on fastsin and fastcos
2025-11-23 working on the code to render navball
2025-11-30 working single core version using DMA, need to optimize and maybe paralelise this
2025-11-30 making the render multicore
2025-12-07 working on the schematics
2025-12-07 adding multiple component (14 semgent and led)
2025-12-08 working on the 14 segment schematics
